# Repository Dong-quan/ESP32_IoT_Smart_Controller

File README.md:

# ESP32 IoT Smart Controller

---

## Table of Contents

1. [Overview](#overview)
2. [Design Requirements](#design-requirements)
3. [Hardware Design](#hardware-design)
   - [Schematic](#schematic)
   - [PCB Layout and Routing](#pcb-layout-and-routing)
4. [Repository Structure](#repository-structure)
5. [Author](#author)

---

## Overview

This project is a compact **Wi-Fi IoT Monitoring and Control Board** designed in KiCad 9.0 (developed as **Mini-Project 11**). Built around the **ESP32-WROOM-32E** module, the board integrates an onboard AC-DC power supply, opto-isolated digital inputs, relay outputs, a high-precision Real-Time Clock (RTC), and dedicated dual USB-A style interfaces for external sensors and a touchscreen HMI display.

External switch inputs are isolated from the logic side using **EL357N-G optocouplers**, protecting the ESP32 from electrical noise and voltage spikes in field environments. The board is powered directly from the 220 V AC mains and steps down the voltage to 5 V DC and 3.3 V DC.

Main functions:

- **Convert power** directly from 220 V AC mains to 5 V DC (`HLK-PM01`) and 3.3 V DC (`AMS1117-3.3`) with built-in fuse, varistor, and EMI filtering.
- **Switch** two AC loads independently using **Omron G5NB-1A-E** relays driven by N-channel MOSFETs.
- **Read** four opto-isolated digital switch inputs (`EL357N-G`) routed through an external USB-A receptacle.
- **Measure** ambient temperature and humidity via an **SHT3x** sensor over I2C, connected through a rugged USB-A style port with selectable 5 V / 3.3 V power (`J8`).
- **Interface** with a **DWIN UART HMI** touchscreen display via a dedicated port (`ERX2`, `ETX2`, 5 V, GND).
- **Maintain** accurate timekeeping with an onboard **DS3231** RTC and `CR1220` coin-cell battery backup.

---

## Design Requirements

### Summary

| Item | Target |
| --- | --- |
| MCU | ESP32-WROOM-32E (Wi-Fi / BLE SoC) |
| Power input | 220 V AC mains (via 4-pin screw terminal) |
| Power rails | 5 V DC (`HLK-PM01` 3 W) and 3.3 V DC (`AMS1117` LDO) |
| Inputs | 4 opto-isolated digital inputs (`EL357N-G`) |
| Outputs | 2 SPST-NO relay outputs (`Omron G5NB-1A-E`, 5 A @ 250 V AC) |
| RTC | `DS3231M` (I2C) with `CR1220` backup battery and trickle-charge circuit |
| External interfaces | Dual USB Type-A receptacles (SHT3x I2C sensor, DWIN UART HMI, 4x switches) |
| Programming & Expansion | 6-pin UART/Boot header (`J4`) and 6-pin I2C/GPIO header (`J1`) |
| Revision | V1.0 |

### Functional requirements

**Power Supply**
- Resettable PTC fuse (`Bourns MF-RG300`), metal oxide varistor (`RV1`), X-capacitor (`1 uF`), and common-mode choke (`UU9.8-HF`) on the 220 V AC input.
- Isolated `HLK-PM01` AC-DC module generating the primary 5 V DC rail.
- `AMS1117-3.3` LDO regulator stepping down 5 V DC to 3.3 V DC for the ESP32 and logic circuits, complete with 5 V and 3.3 V power indicator LEDs and a `5.1 V` Zener clamp (`Z2`) on the VDD line.

**Inputs**
- Four opto-isolated digital channels (`U3`, `U4`, `U6`, `U13` using `EL357N-G`) with input RC filtering and pull-up resistors to 3.3 V.
- External switch connections (`SW1`–`SW4`) wired through stacked USB Type-A receptacle `J3`.

**Outputs**
- Two relay channels (`RL1`, `RL2` using `G5NB-1A-E`) switching the AC Neutral line to `LOAD1` and `LOAD2` on the main screw terminal (`J9`).
- Driven by `IRLML0030` N-channel MOSFETs (`Q1`, `Q2`) with `1N4007` flyback diodes (`D1`, `D2`) and status indicator LEDs (`LE3`, `LE4`).

**Microcontroller, RTC, and Peripherals**
- **ESP32-WROOM-32E** with tactile Reset (`ERST1`) and Boot (`EBOOT1`) buttons.
- **DS3231M** RTC communicating over I2C (`SCL1`, `SDA1`) with `CR1220` battery backup (`BT1`) and a diode-resistor charging path (`D7`, `D8`, `R27`).
- Stacked USB Type-A receptacle `J2`:
  - Port A: **DWIN HMI** interface (`5V`, `ERX2`, `ETX2`, `GND`).
  - Port B: **SHT3x Sensor** interface (`VB`, `SDA1`, `SCL1`, `GND`) with a 3-pin jumper (`J8`) to select `5V` or `3.3V` for `VB`.

---

## Hardware Design

### Schematic

Key components from the schematic (`Bai11.kicad_sch`):

| Block | Main components |
| --- | --- |
| MCU | `ESP32-WROOM-32E`, `B3U-1000P` tactile switches (`EBOOT1`, `ERST1`), `5.1V` Zener (`Z2`) |
| Power | `HLK-PM01` (AC-DC 5 V), `AMS1117-3.3` LDO, `Bourns MF-RG300` fuse, 12 mm disc varistor, `UU9.8-HF` EMI filter |
| Isolated Inputs | 4x `EL357N-G` optocouplers (`U3`, `U4`, `U6`, `U13`), dual USB-A connector (`J3`) |
| Relay Outputs | 2x `Omron G5NB-1A-E` 5 V relays (`RL1`, `RL2`), 2x `IRLML0030` MOSFETs (`Q1`, `Q2`), `1N4007` flyback diodes, 4-pin 9.5 mm pitch screw terminal (`J9`) |
| Timekeeping (RTC) | `DS3231M` (`SOIC-16W`), `CR1220` SMD battery holder (`BT1`), `1N4007` diodes (`D7`, `D8`) |
| Sensor & HMI Ports | Dual USB-A connector (`J2`), 1x03 voltage selector header (`J8`), 1x06 programming header (`J4`), 1x06 GPIO/I2C header (`J1`) |

### PCB Layout and Routing

The PCB is a 2-layer FR-4 board (`1.6 mm` thickness, `1 oz` copper) with clear physical separation between the 220 V AC high-voltage section (left side) and the low-voltage logic/wireless section (right side). High-voltage warning silkscreens and an antenna keepout zone for the ESP32 module are strictly maintained.

**Layout**

| Top layer | Bottom layer |
| :---: | :---: |
|  |  |

**3D view**

| Top side | Bottom side |
| :---: | :---: |
|  |  |

---

## Repository Structure

```
ESP32_IoT_Smart_Controller/
├── Images/                     # PCB layout and 3D render images
├── Bai11.kicad_pro             # KiCad 9.0 project file
├── Bai11.kicad_prl             # Project local settings
├── Bai11.kicad_sch             # Complete circuit schematic
├── Bai11.kicad_pcb             # 2-layer PCB layout file
├── Bai11.pdf                   # Exported schematic PDF
├── Bai11.step                  # 3D STEP model of the assembled board
├── fp-info-cache
└── README.md
```
---

## Author

- **Huynh Vo Phuc Loc**
- GitHub: [Dong-quan](https://github.com/Dong-quan)

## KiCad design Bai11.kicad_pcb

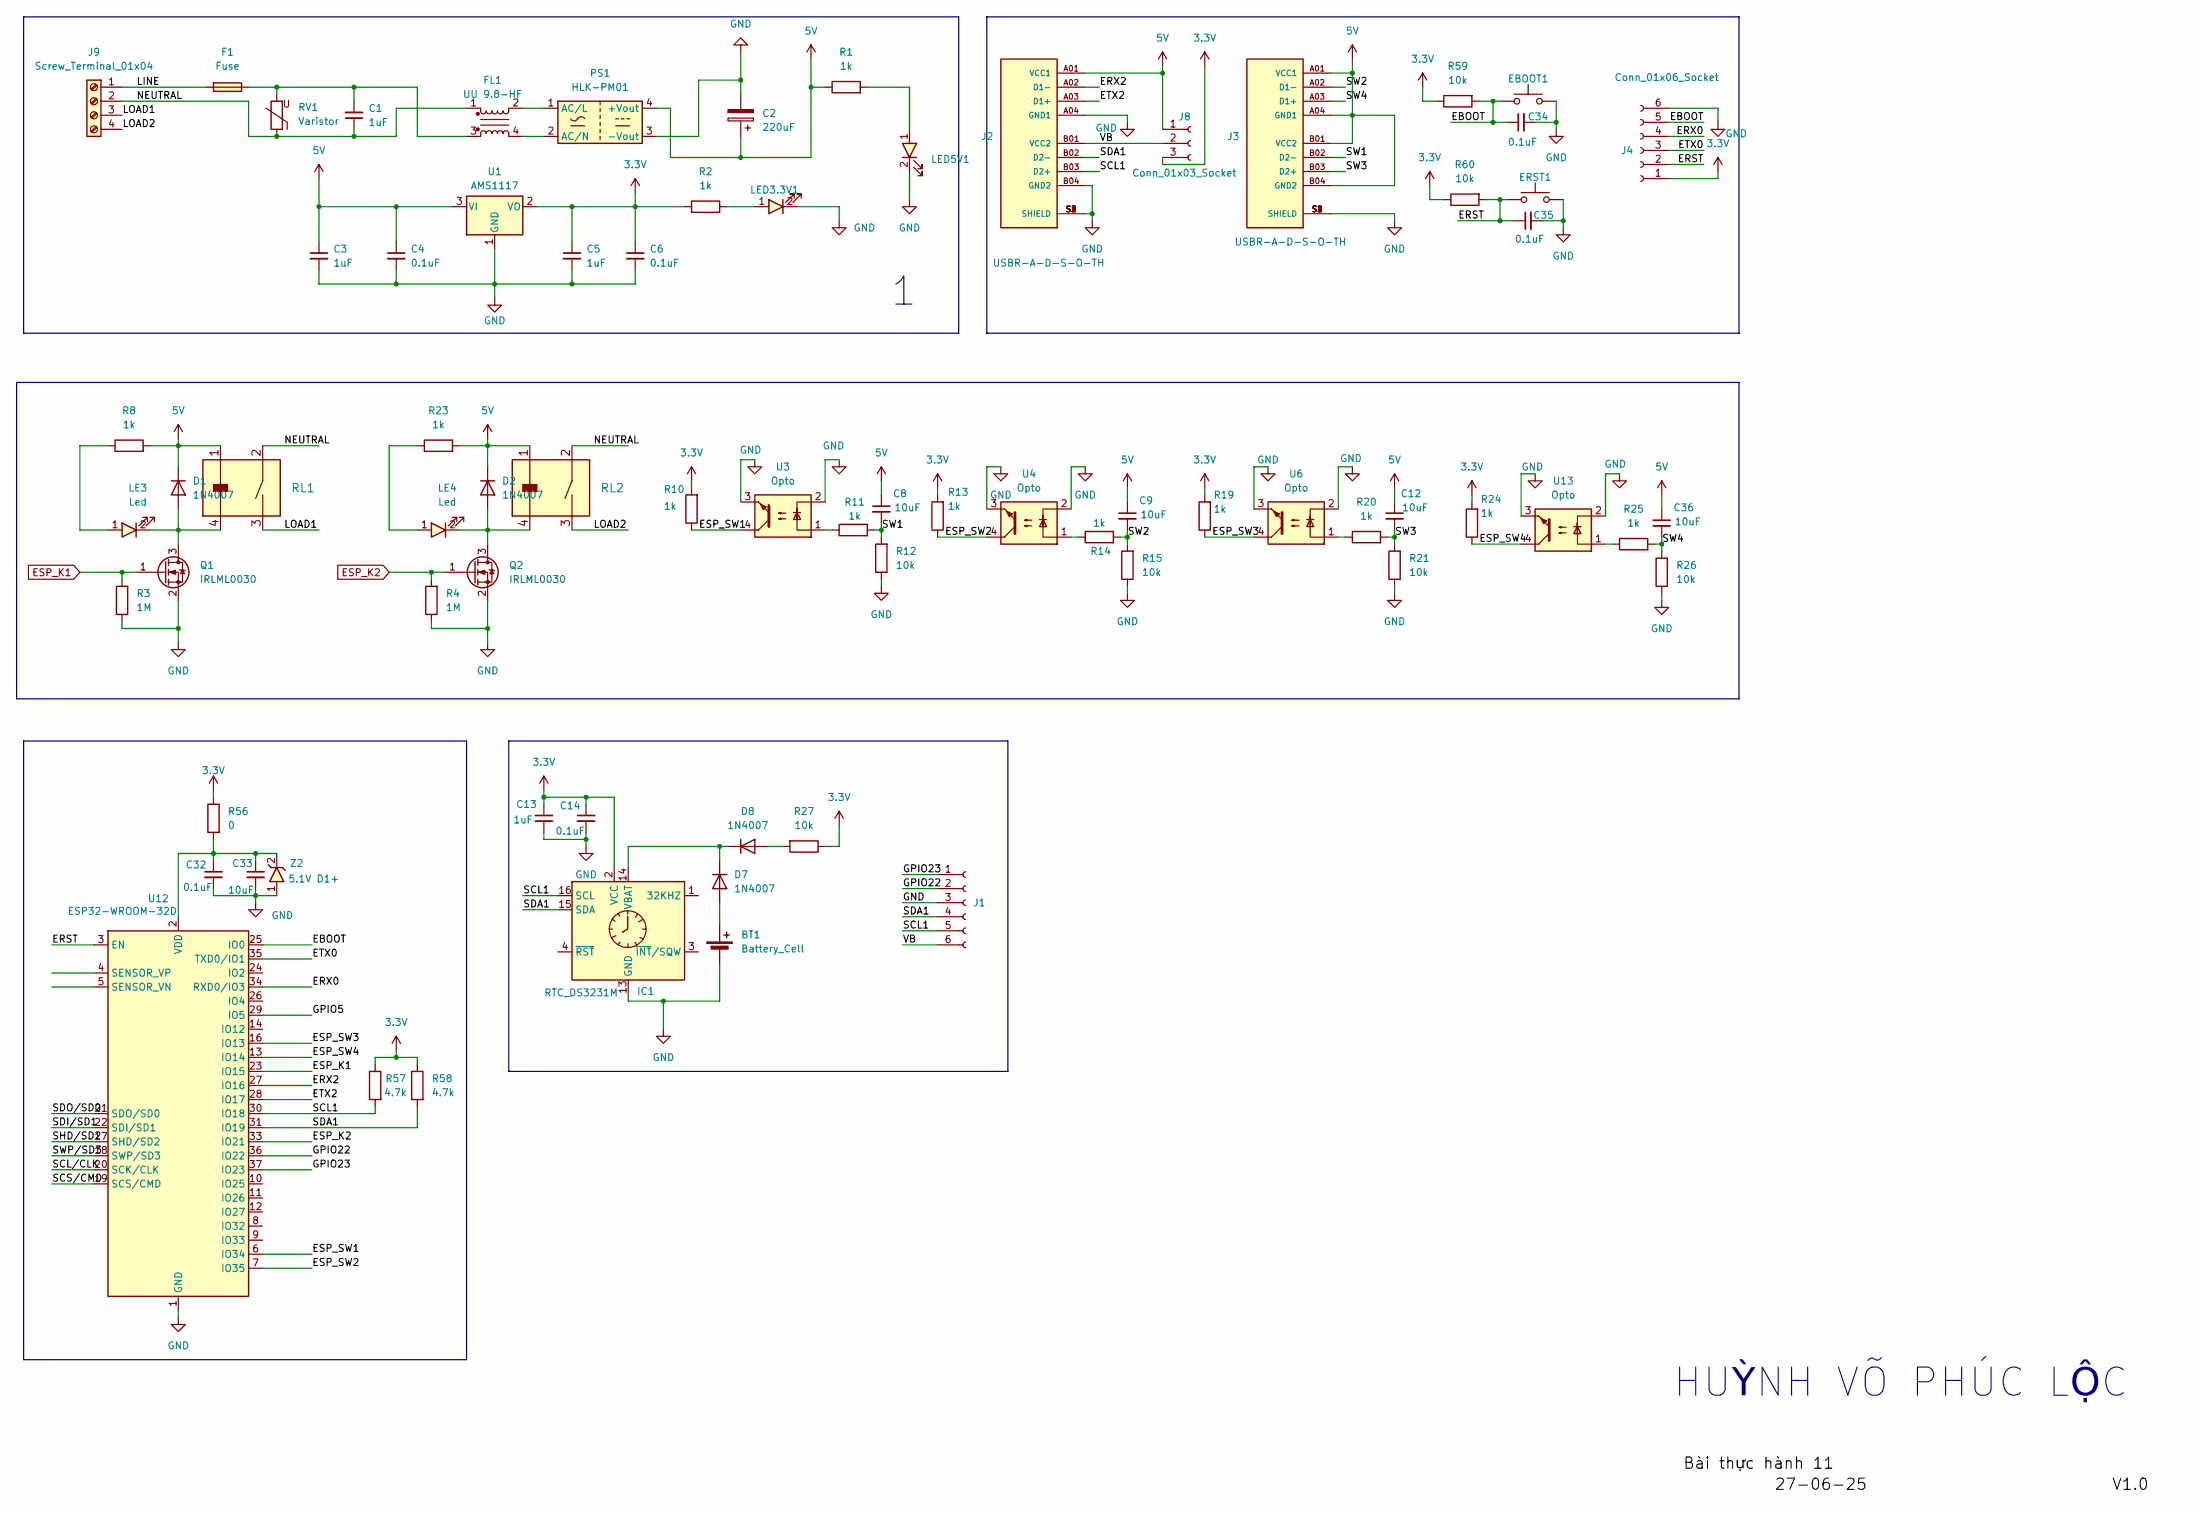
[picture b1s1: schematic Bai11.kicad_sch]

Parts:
BT1: Battery_Cell; BatteryHolder-SMD-CR1220
C1: 1uF; C-Polyester-Rect-L16.5mm-W5.0mm-P15.00mm-MKT
C2: 220uF; CP_Elec_8x10.5
C3, C5, C13: 1uF; C_0603
C4, C6, C14, C32, C34, C35: 0.1uF; C_0603
C8, C9, C12, C33, C36: 10uF; C_0603
D1, D2, D7, D8: 1N4007; D_SOD-123F
EBOOT1: SW_SPST_B3U-1000P
ERST1: SW_SPST_B3U-1000P
F1: Fuse; Fuse_Bourns_MF-RG300
FL1: UU 9.8-HF; ACFilterChoke-UU9.8
IC1: RTC_DS3231M; SOIC-16W_7.5x10.3mm_P1.27mm
J1, J4: Conn_01x06_Socket; PinHeader_1x06_P2.54mm_Vertical
J2, J3: USBR-A-D-S-O-TH; SAMTEC_USBR-A-D-S-O-TH
J8: Conn_01x03_Socket; PinHeader_1x03_P2.54mm_Vertical
J9: Screw_Terminal_01x04; TerminalBlock-Vert-THT-4P-P9.5mm-Screw_HB9500
LE3, LE4: Led; LED_D3.0mm
LED3.3V1, LED5V1: Led; LED_D3.0mm
PS1: HLK-PM01; Converter_ACDC_Hi-Link_HLK-PMxx
Q1, Q2: IRLML0030; SOT-23
R1, R2, R8, R10, R11, R13, R14, R19, R20, R23, R24, R25: 1k; R_0603
R3, R4: 1M; R_0603
R12, R15, R21, R26, R27, R59, R60: 10k; R_0603
R56: 0; R_0603
R57, R58: 4.7k; R_0603
RL1, RL2: Relay_G5NB-1A-E_DC5; Relay-G5NB_1A_E_DC5
RV1: Varistor; Varistor-RV-Disc-D12mm-W5.8mm-P7.5mm
U1: AMS1117; SOT233
U3, U4, U6, U13: Opto; OptoIsolation-EL357N-G
U12: ESP32-WROOM-32D; ESP32-WROOM-32E
Z2: 5.1V D1+; D_0603_1608Metric

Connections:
3.3V: C5.1, C6.1, C13.1, C14.1, IC1.2 (VCC), J4.1, J8.3, R2.1, R10.2, R13.2, R19.2, R24.2, R27.1, R56.1, R57.1, R58.1, R59.1, R60.1, U1.2 (VO)
5V: C2.1, C3.1, C4.1, C8.1, C9.1, C12.1, C36.1, D1.1 (K), D2.1 (K), J2.A01 (VCC1), J3.A01 (VCC1), J3.A04 (GND1), J3.B01 (VCC2), J3.B04 (GND2), J8.1, PS1.4 (+Vout), R1.1, R8.2, R23.2, RL1.1, RL2.1, U1.3 (VI)
/EBOOT: C34.1, EBOOT1.1, J4.5, R59.2, U12.25 (IO0)
/ERST: C35.1, ERST1.1, J4.2, R60.2, U12.3 (EN)
/ERX0: J4.4, U12.34 (RXD0/IO3)
/ERX2: J2.A02 (D1-), U12.27 (IO16)
/ESP_SW1: R10.1, U3.4, U12.6 (IO34)
/ESP_SW2: R13.1, U4.4, U12.7 (IO35)
/ESP_SW3: R19.1, U6.4, U12.16 (IO13)
/ESP_SW4: R24.1, U12.13 (IO14), U13.4
/ETX0: J4.3, U12.35 (TXD0/IO1)
/ETX2: J2.A03 (D1+), U12.28 (IO17)
/GPIO5: U12.29 (IO5)
/GPIO22: J1.2, U12.36 (IO22)
/GPIO23: J1.1, U12.37 (IO23)
/LINE: F1.1, J9.1
/LOAD1: J9.3, RL1.3
/LOAD2: J9.4, RL2.3
/NEUTRAL: C1.1, FL1.1, J9.2, RL1.2, RL2.2, RV1.1
/SCL1: IC1.16 (SCL), J1.5, J2.B03 (D2+), R57.2, U12.30 (IO18)
/SCL/CLK: U12.20 (SCK/CLK)
/SCS/CMD: U12.19 (SCS/CMD)
/SDA1: IC1.15 (SDA), J1.4, J2.B02 (D2-), R58.2, U12.31 (IO19)
/SDI/SD1: U12.22 (SDI/SD1)
/SDO/SD0: U12.21 (SDO/SD0)
/SHD/SD2: U12.17 (SHD/SD2)
/SW1: C8.2, J3.B02 (D2-), R11.2, R12.2
/SW2: C9.2, J3.A02 (D1-), R14.2, R15.2
/SW3: C12.2, J3.B03 (D2+), R20.2, R21.2
/SW4: C36.2, J3.A03 (D1+), R25.2, R26.2
/SWP/SD3: U12.18 (SWP/SD3)
/VB: J1.6, J2.B01 (VCC2), J8.2
ESP_K1: Q1.1 (G), R3.2, U12.23 (IO15)
ESP_K2: Q2.1 (G), R4.2, U12.33 (IO21)
GND: BT1.2 (-), C2.2, C3.2, C4.2, C5.2, C6.2, C13.2, C14.2, C32.2, C33.2, C34.2, C35.2, EBOOT1.2, ERST1.2, IC1.5 (GND), IC1.6 (GND), IC1.7 (GND), IC1.8 (GND), IC1.9 (GND), IC1.10 (GND), IC1.11 (GND), IC1.12 (GND), IC1.13 (GND), J1.3, J2.A04 (GND1), J2.B04 (GND2), J2.S1 (SHIELD), J2.S2 (SHIELD), J2.S3 (SHIELD), J2.S4 (SHIELD), J3.S1 (SHIELD), J3.S2 (SHIELD), J3.S3 (SHIELD), J3.S4 (SHIELD), J4.6, LED3.3V1.2, LED5V1.2, PS1.3 (-Vout), Q1.2 (S), Q2.2 (S), R3.1, R4.1, R12.1, R15.1, R21.1, R26.1, U1.1 (GND), U3.2, U3.3, U4.2, U4.3, U6.2, U6.3, U12.1 (GND), U12.15 (GND), U12.38 (GND), U12.39 (GND), U13.2, U13.3, Z2.1
unnamed: BT1.1 (+), D7.2 (A)
unnamed: C1.2, F1.2, FL1.3, RV1.2
unnamed: D1.2 (A), LE3.2, Q1.3 (D), RL1.4
unnamed: D2.2 (A), LE4.2, Q2.3 (D), RL2.4
unnamed: D7.1 (K), D8.1 (K), IC1.14 (VBAT)
unnamed: D8.2 (A), R27.2
unnamed: LE3.1, R8.1
unnamed: LE4.1, R23.1
unnamed: LED3.3V1.1, R2.2
unnamed: LED5V1.1, R1.2
unnamed: FL1.2, PS1.1 (AC/L)
unnamed: FL1.4, PS1.2 (AC/N)
unnamed: R11.1, U3.1
unnamed: R14.1, U4.1
unnamed: R20.1, U6.1
unnamed: R25.1, U13.1
unnamed: C32.1, C33.1, R56.2, U12.2 (VDD), Z2.2

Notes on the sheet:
HUỲNH VÕ PHÚC LỘC

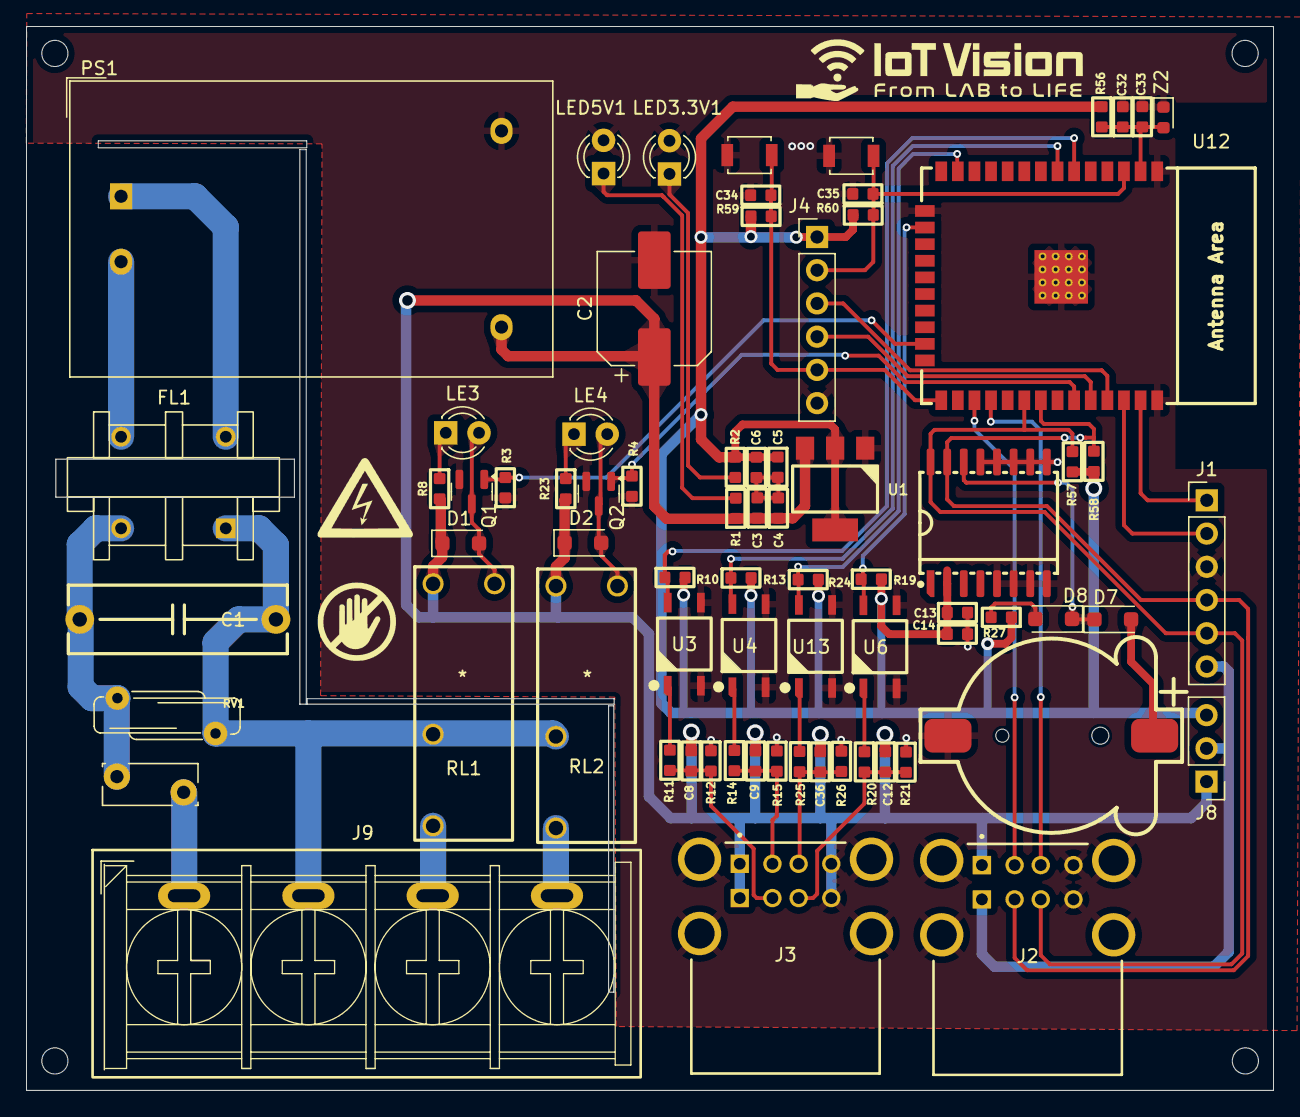
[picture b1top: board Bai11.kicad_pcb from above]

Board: 2 copper layers, 95.3 x 81.3 mm, 73 parts (0 on the bottom side), 45 nets.
